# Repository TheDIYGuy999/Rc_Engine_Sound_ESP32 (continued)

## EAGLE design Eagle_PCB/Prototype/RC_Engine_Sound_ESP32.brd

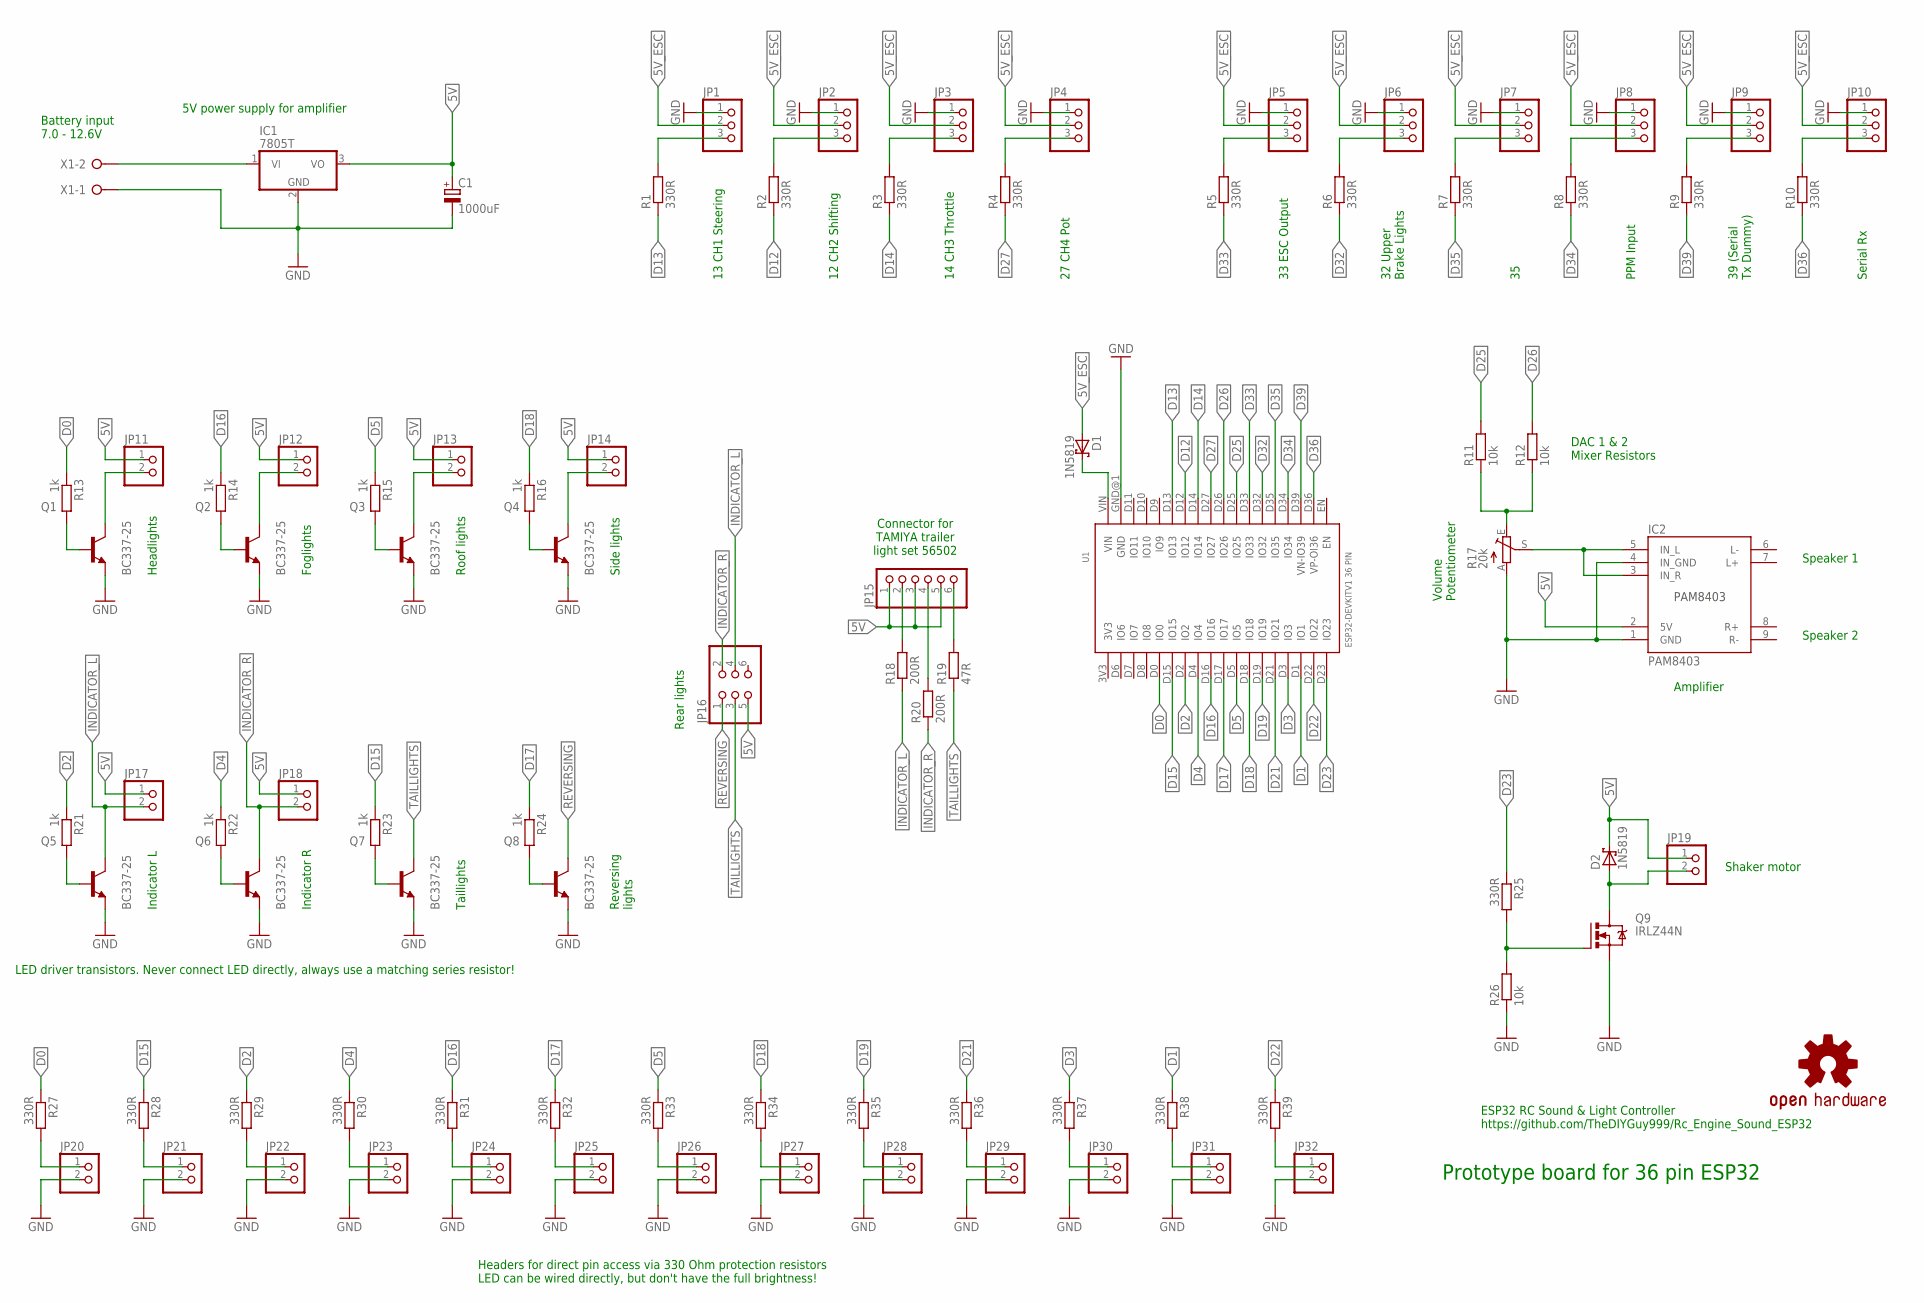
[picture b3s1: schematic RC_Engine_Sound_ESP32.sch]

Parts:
C1: 1000uF; E5-10,5
D1, D2: 1N5819; DO35-7
IC1: 7805T; TO220H
IC2: PAM8403
JP1, JP2, JP3, JP4, JP5, JP6, JP7, JP8, JP9, JP10: PINHD-1X3; 1X03
JP11, JP12, JP13, JP14, JP17, JP18, JP19, JP20, JP21, JP22, JP23, JP24, JP25, JP26, JP27, JP28, JP29, JP30, JP31, JP32: PINHD-1X2; 1X02
JP15: PINHD-1X6; 1X06
JP16: PINHD-2X3; 2X03
LOGO1: OSHW-LOGOM; OSHW-LOGO-M
Q1, Q2, Q3, Q4, Q5, Q6, Q7, Q8: BC337-25; TO92
Q9: IRLZ44N; TO220BV
R1, R2, R3, R4, R5, R6, R7, R8, R9, R10, R25, R27, R28, R29, R30, R31, R32, R33, R34, R35, R36, R37, R38, R39: 330R; 0207/2V
R11, R12: 10k; 0207/10
R13, R14, R15, R16, R21, R22, R23, R24: 1k; 0207/2V
R17: 20k; S64W
R18, R20: 200R; 0207/2V
R19: 47R; 0207/2V
R26: 10k; 0207/2V
U1: ESP32DEVKITV1; ESP32-DEVKITV1
X1: W237-02P; W237-132

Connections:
5V: C1.+, D2.C, IC1.3 (VO), IC2.2 (5V), JP11.1, JP12.1, JP13.1, JP14.1, JP15.1, JP15.3, JP15.5, JP16.5, JP17.1, JP18.1, JP19.1
5V_ESC: D1.A, JP1.2, JP2.2, JP3.2, JP4.2, JP5.2, JP6.2, JP7.2, JP8.2, JP9.2, JP10.2
BAT+: IC1.1 (VI), X1.2
D1: R38.1, U1.D1 (IO1)
D2: R21.1, R29.1, U1.D2 (IO2)
D4: R22.1, R30.1, U1.D4 (IO4)
D5: R15.1, R33.1, U1.D5 (IO5)
D12: R2.1, U1.D12 (IO12)
D13: R1.1, U1.D13 (IO13)
D14: R3.1, U1.D14 (IO14)
D15: R23.1, R28.1, U1.D15 (IO15)
D16: R14.1, R31.1, U1.D16 (IO16)
D17: R24.1, R32.1, U1.D17 (IO17)
D18: R16.1, R34.1, U1.D18 (IO18)
D19: R35.1, U1.D19 (IO19)
D21: R36.1, U1.D21 (IO21)
D22: R39.1, U1.D22 (IO22)
D23: R25.1, U1.D23 (IO23)
D25: R11.2, U1.D25 (IO25)
D26: R12.2, U1.D26 (IO26)
D27: R4.1, U1.D27 (IO27)
D32: R6.1, U1.D32 (IO32)
D33: R5.1, U1.D33 (IO33)
D34: R8.1, U1.D34 (IO34)
D35: R7.1, U1.D35 (IO35)
D36: R10.1, U1.D36 (VP-OI36)
D39: R9.1, U1.D39 (VN-IO39)
GND: C1.-, IC1.2 (GND), IC2.1 (GND), IC2.4 (IN_GND), JP1.1, JP2.1, JP3.1, JP4.1, JP5.1, JP6.1, JP7.1, JP8.1, JP9.1, JP10.1, JP20.2, JP21.2, JP22.2, JP23.2, JP24.2, JP25.2, JP26.2, JP27.2, JP28.2, JP29.2, JP30.2, JP31.2, JP32.2, Q1.1 (E), Q2.1 (E), Q3.1 (E), Q4.1 (E), Q5.1 (E), Q6.1 (E), Q7.1 (E), Q8.1 (E), Q9.S, R17.A, R26.1, U1.GND@1 (GND), X1.1
INDICATOR_L: JP16.4, JP17.2, Q5.3 (C), R18.1
INDICATOR_R: JP16.2, JP18.2, Q6.3 (C), R20.1
unnamed: IC2.3 (IN_R), IC2.5 (IN_L), R17.S
unnamed: R11.1, R12.1, R17.E
unnamed: JP1.3, R1.2
unnamed: Q9.G, R25.2, R26.2
unnamed: JP2.3, R2.2
unnamed: JP3.3, R3.2
unnamed: JP4.3, R4.2
unnamed: JP5.3, R5.2
unnamed: D1.C, U1.VIN
unnamed: JP6.3, R6.2
unnamed: JP7.3, R7.2
unnamed: JP8.3, R8.2
unnamed: JP9.3, R9.2
unnamed: JP10.3, R10.2
unnamed: D2.A, JP19.2, Q9.D
unnamed: Q1.2 (B), R13.2
unnamed: Q2.2 (B), R14.2
unnamed: JP11.2, Q1.3 (C)
unnamed: JP12.2, Q2.3 (C)
unnamed: Q7.2 (B), R23.2
unnamed: JP15.2, R18.2
unnamed: Q5.2 (B), R21.2
unnamed: JP15.4, R20.2
unnamed: Q6.2 (B), R22.2
unnamed: JP15.6, R19.2
unnamed: Q8.2 (B), R24.2
unnamed: Q3.2 (B), R15.2
unnamed: JP13.2, Q3.3 (C)
unnamed: Q4.2 (B), R16.2
unnamed: JP14.2, Q4.3 (C)
unnamed: JP21.1, R28.2
unnamed: JP22.1, R29.2
unnamed: JP23.1, R30.2
unnamed: JP24.1, R31.2
unnamed: JP25.1, R32.2
unnamed: JP26.1, R33.2
unnamed: JP27.1, R34.2
unnamed: JP28.1, R35.2
unnamed: JP29.1, R36.2
unnamed: JP30.1, R37.2
unnamed: JP31.1, R38.2
unnamed: JP32.1, R39.2
unnamed: JP20.1, R27.2
REVERSING: JP16.1, Q8.3 (C)
TAILLIGHTS: JP16.3, Q7.3 (C), R19.1

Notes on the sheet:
Speaker 1
Speaker 2
13 CH1 Steering
12 CH2 Shifting
14 CH3 Throttle
27 CH4 Pot
33 ESC Output
32 Upper Brake Lights
PPM Input
39 (Serial Tx Dummy)
Serial Rx
DAC 1 & 2 Mixer Resistors
Amplifier
Volume Potentiometer
5V power supply for amplifier
Battery input 7.0 - 12.6V
Prototype board for 36 pin ESP32
Shaker motor
Headlights
Foglights
Taillights
Indicator L
Indicator R
Roof lights
Side lights
Reversing lights
Connector for TAMIYA trailer light set 56502
Rear lights
ESP32 RC Sound & Light Controller https://github.com/TheDIYGuy999/Rc_Engine_Sound_ESP32
Headers for direct pin access via 330 Ohm protection resistors LED can be wired directly, but don't have the full brightness!
LED driver transistors. Never connect LED directly, always use a matching series resistor!

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
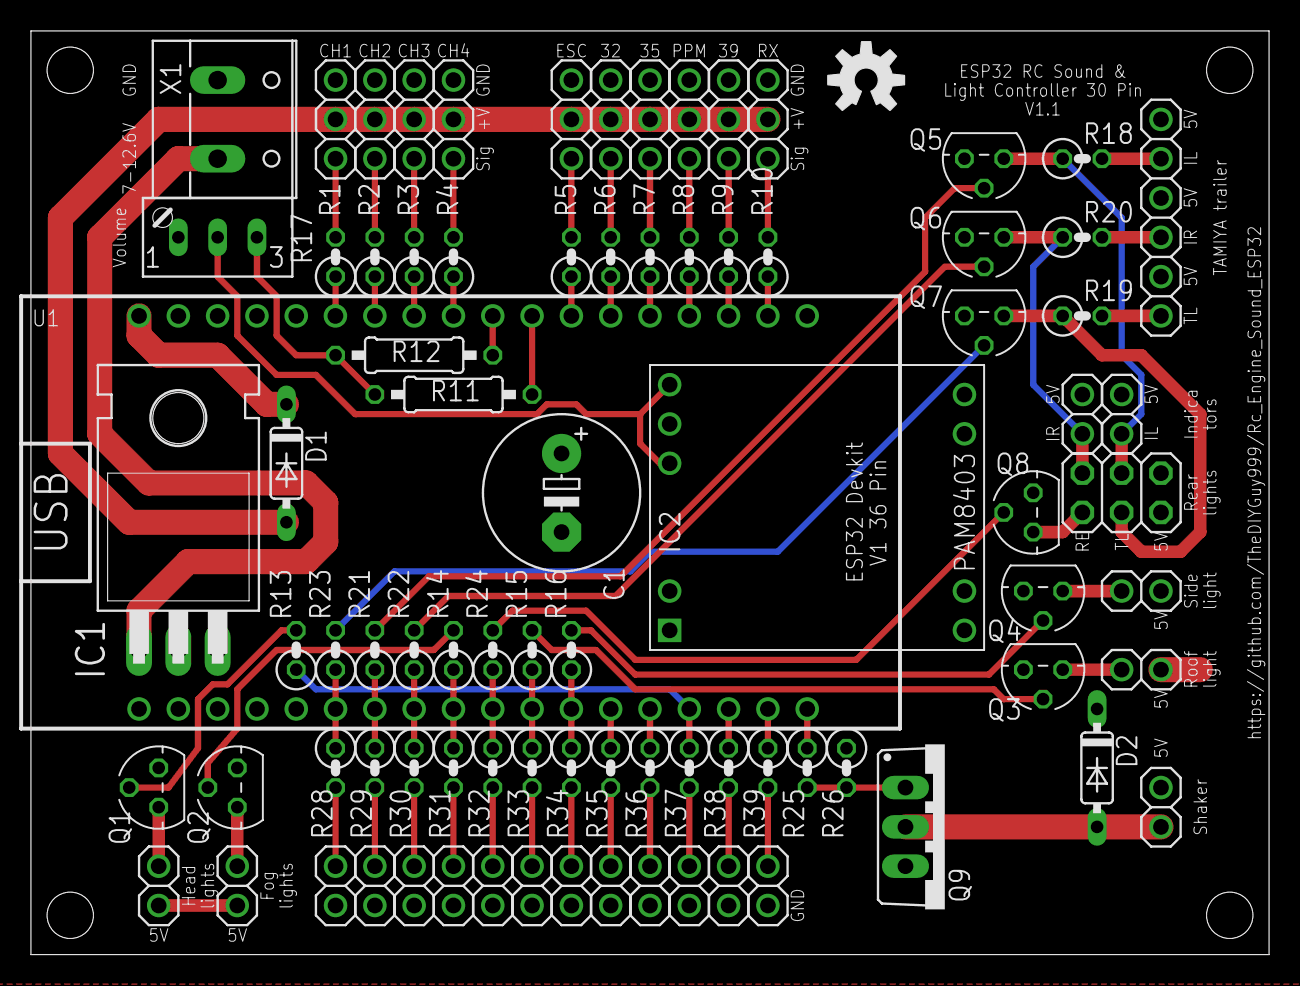
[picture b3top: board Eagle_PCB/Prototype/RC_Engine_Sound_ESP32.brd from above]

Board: 2 copper layers, 80.0 x 59.7 mm, 86 parts (0 on the bottom side), 75 nets.

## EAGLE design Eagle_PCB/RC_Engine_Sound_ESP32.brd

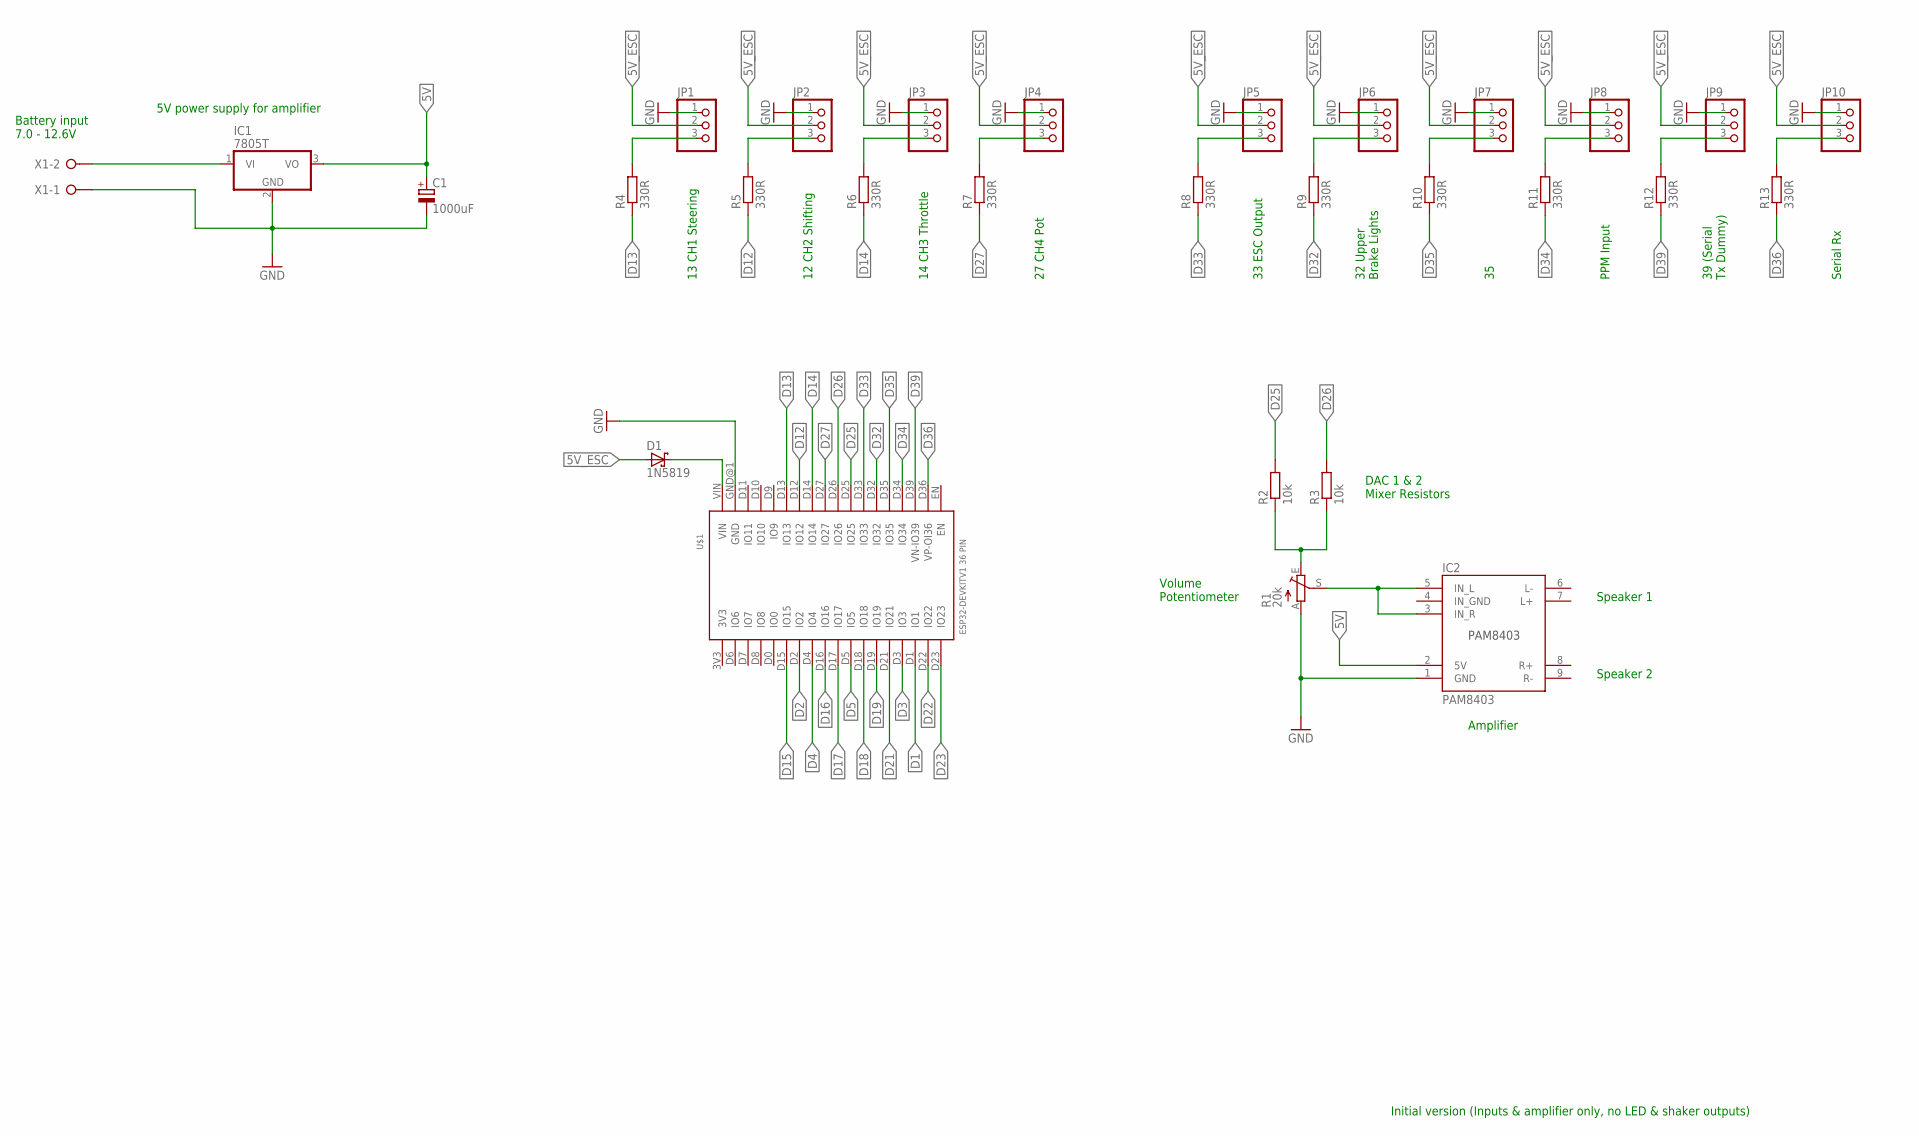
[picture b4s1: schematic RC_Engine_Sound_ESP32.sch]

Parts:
C1: 1000uF; E5-10,5
D1: 1N5819; DO35-7
IC1: 7805T; TO220H
IC2: PAM8403
JP1, JP2, JP3, JP4, JP5, JP6, JP7, JP8, JP9, JP10: PINHD-1X3; 1X03
R1: 20k; S64W
R2, R3: 10k; 0207/10
R4, R5, R6, R7, R8, R9, R10, R11, R12, R13: 330R; 0207/2V
U$1: ESP32DEVKITV1; ESP32-DEVKITV1
X1: W237-02P; W237-132

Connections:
5V: C1.+, IC1.3 (VO), IC2.2 (5V)
5V_ESC: D1.A, JP1.2, JP2.2, JP3.2, JP4.2, JP5.2, JP6.2, JP7.2, JP8.2, JP9.2, JP10.2
D1: U$1.D1 (IO1)
D2: U$1.D2 (IO2)
D3: U$1.D3 (IO3)
D4: U$1.D4 (IO4)
D5: U$1.D5 (IO5)
D12: R5.1, U$1.D12 (IO12)
D13: R4.1, U$1.D13 (IO13)
D14: R6.1, U$1.D14 (IO14)
D15: U$1.D15 (IO15)
D16: U$1.D16 (IO16)
D17: U$1.D17 (IO17)
D18: U$1.D18 (IO18)
D19: U$1.D19 (IO19)
D21: U$1.D21 (IO21)
D22: U$1.D22 (IO22)
D23: U$1.D23 (IO23)
D25: R2.2, U$1.D25 (IO25)
D26: R3.2, U$1.D26 (IO26)
D27: R7.1, U$1.D27 (IO27)
D32: R9.1, U$1.D32 (IO32)
D33: R8.1, U$1.D33 (IO33)
D34: R11.1, U$1.D34 (IO34)
D35: R10.1, U$1.D35 (IO35)
D36: R13.1, U$1.D36 (VP-OI36)
D39: R12.1, U$1.D39 (VN-IO39)
GND: C1.-, IC1.2 (GND), IC2.1 (GND), JP1.1, JP2.1, JP3.1, JP4.1, JP5.1, JP6.1, JP7.1, JP8.1, JP9.1, JP10.1, R1.A, U$1.GND@1 (GND), X1.1
unnamed: IC2.3 (IN_R), IC2.5 (IN_L), R1.S
unnamed: R1.E, R2.1, R3.1
unnamed: JP1.3, R4.2
unnamed: IC1.1 (VI), X1.2
unnamed: JP2.3, R5.2
unnamed: JP3.3, R6.2
unnamed: JP4.3, R7.2
unnamed: JP5.3, R8.2
unnamed: D1.C, U$1.VIN
unnamed: JP6.3, R9.2
unnamed: JP7.3, R10.2
unnamed: JP8.3, R11.2
unnamed: JP9.3, R12.2
unnamed: JP10.3, R13.2

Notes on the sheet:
Speaker 1
Speaker 2
13 CH1 Steering
12 CH2 Shifting
14 CH3 Throttle
27 CH4 Pot
33 ESC Output
32 Upper Brake Lights
PPM Input
39 (Serial Tx Dummy)
Serial Rx
DAC 1 & 2 Mixer Resistors
Amplifier
Volume Potentiometer
5V power supply for amplifier
Battery input 7.0 - 12.6V
Initial version (Inputs & amplifier only, no LED & shaker outputs)

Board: 2 copper layers, 29 parts (0 on the bottom side), 29 nets, no tracks yet.

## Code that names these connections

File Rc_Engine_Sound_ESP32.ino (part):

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// ERROR CODES (INDICATOR LIGHTS)
// =======================================================================================================
//
/* Constantly on = no SBUS signal (check "sbusInverted" true / false in "2_adjustmentsRemote.h")
   Number of blinks = this channel signal is not between 1400 and 1600 microseconds and can't be auto calibrated
   (check channel trim settings)
*/
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// provides short circuit protection. Also works on the serial Rx pin "VP" (36)
// ------------------------------------------------------------------------------------

// Serial command pins for SBUS & IBUS -----
#define COMMAND_RX 36 // pin 36, labelled with "VP", connect it to "Micro RC Receiver" pin "TXO"
#define COMMAND_TX 39 // pin 39, labelled with "VN", only used as a dummy, not connected

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#define INDICATOR_LEFT_PIN 2 // Orange left indicator (turn signal) light
#define INDICATOR_RIGHT_PIN 4 // Orange right indicator (turn signal) light
#define FOGLIGHT_PIN 16 // (16 = RX2) Fog lights
#define REVERSING_LIGHT_PIN 17 // (TX2) White reversing light
#define ROOFLIGHT_PIN 5 // Roof lights (high beam, if "define SEPARATE_FULL_BEAM")
#define SIDELIGHT_PIN 18 // Side lights (connect roof ligthts here, if "define SEPARATE_FULL_BEAM")
#define BEACON_LIGHT2_PIN 19 // Blue beacons light
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#define COUPLER_SWITCH_PIN 32 // switch for trailer coupler sound
#endif

#define SHAKER_MOTOR_PIN 23 // Shaker motor (shaking truck while idling and engine start / stop)

#define DAC1 25 // connect pin25 (do not change the pin) to a 10kOhm resistor
#define DAC2 26 // connect pin26 (do not change the pin) to a 10kOhm resistor
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  static uint32_t curHornSample = 0;                           // Index of currently loaded horn sample
  static uint32_t curSirenSample = 0;                          // Index of currently loaded siren sample
  static uint32_t curSound1Sample = 0;                         // Index of currently loaded sound1 sample
  static uint32_t curReversingSample = 0;                      // Index of currently loaded reversing beep sample
  static uint32_t curIndicatorSample = 0;                      // Index of currently loaded indicator tick sample
  static uint32_t curWastegateSample = 0;                      // Index of currently loaded wastegate sample
  static uint32_t curBrakeSample = 0;                          // Index of currently loaded brake sound sample
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
#if not defined SPI_DASHBOARD
  sideLight.begin(SIDELIGHT_PIN, 8, 20000); // Timer 8, 20kHz
  beaconLight1.begin(BEACON_LIGHT1_PIN, 9, 20000); // Timer 9, 20kHz
  beaconLight2.begin(BEACON_LIGHT2_PIN, 10, 20000); // Timer 10, 20kHz
#endif

#if defined THIRD_BRAKLELIGHT
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  sbusInit = false;
  Serial.println("Initializing SBUS, check transmitter & receiver (sbusInverted true / false OK?)...");
  while (!sbusInit) {
    readSbusCommands(); // SBUS communication (pin 36)
  }
  Serial.println("SBUS initialization done!");

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    brakeLight.pwm(255 - crankingDim); // Brakelight on
  }
  else {
    tailLight.pwm(constrain(brightness - (crankingDim / 2), (brightness / 2), 255)); // Taillights (reduced brightness)
    brakeLight.pwm(constrain(brightness - (crankingDim / 2), (brightness / 2), 255)); // Brakelight (reduced brightness)
  }
}
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
    case 4: // roof & side & head & fog lights ---------------------------------------------------------------------
#ifdef NO_FOGLIGHTS
      lightsState = 5; // Skip foglights
#endif
      cabLight.off();
      sideLight.pwm(constrain(sideLightsBrightness - crankingDim, (sideLightsBrightness / 2), 255));
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void loop() {

#if defined SBUS_COMMUNICATION
  readSbusCommands(); // SBUS communication (pin 36)
  mcpwmOutput(); // PWM servo signal output

#elif defined IBUS_COMMUNICATION
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
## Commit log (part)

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2019-12-03 Initial version 0.1
2019-12-03 V0.2: many new sounds added
2019-12-05 V0.3: horn added, plays together with engine sound!
2019-12-07 V0.4: volume offset bug fixed, new sounds
2019-12-08 V0.4: volume offset bug fixed, new sounds, schematic
2019-12-09 V0.5: added PWM horn triggering option, Jaguar car and UP locomotive
2019-12-10 v0.6: fixed slow engine RPM response
2019-12-10 v0.7: "gap" bug between sounds in PWM mode fixed, 2 sounds in PWM mode
2019-12-10 v0.8: many new sounds, volume offset bug fixed again
2019-12-14 v0.9: Humvee Diesel sound and truck pneumatic brake release sound added
2019-12-15 v1.0: engine shut off sequence, truck air brakes
2019-12-16 v1.1: Truck reversing peep sound added
2019-12-17 v1.2: control for lights added
2019-12-22 v1.4: Indicator (turn signal) support added
2019-12-24 v1.51: solved redefinition issue
2019-12-27 v1.6: serial control mode added, more sounds, more lights
2019-12-31 v1.7: engine vibration shaker support added
2020-01-04 v1.8: throttle dependent engine volume, indicator ticking sound, new sounds
2020-01-10 v1.9: initial PPM input support for throttle and steering
2020-01-12 v2.0: Mack truck added, experimental features added, statusLED library update required!
2020-01-18 v2.1: adjustable turbo sound, Cat 3406B, VW beetle, indicator direction adjustable
2020-01-19 v2.2: vehicle mass simulation (ESC control) added, LED pins changed, Scania R620 sound
2020-01-19 v2.2: vehicle mass simulation (ESC control) added, LED pins changed, Scania R620 sound added
2020-01-20 v2.3: many detail optimisations like brake lights, reversing lights, air brake sound
2020-01-22 Minor reversing bug fixed, failsafe mode for Serial & PWM communication mode
2020-02-08 v2.5: 3rd brake light added, realistic top speed, smoother acceleration & deceleration
2020-02-20 v2.7: inertia simulation transmission gear dependent, new horns
2020-02-21 v2.8: virtual clutch added, variable acceleration speed, better brakes
2020-02-22 v2.9: throttle now automatically altered while TAMIYA 3 speed gearbox shifting
2020-02-23 v2.91: minor bugfixes according to readme.md
2020-02-24 v3.0: clutch engaging changed to prevent it from excessive slipping
2020-02-25 V3.1: Scania R620 & other sounds added
2020-02-27 V3.2: added wastegate, Unimog U 1000, AM General M35
2020-03-04 v3.3: many changes according to readme
2020-03-08 v3.4: separate Diesel knock with fixed sampling rate, many other changes
2020-03-14 v3.5: diesel knock triggering bug fixed, new sounds and more
2020-03-15 Cooling fan sound, Tatra 813 V12, Scania 50 ton added
2020-03-15 v3.6: Cooling fan sound, Tatra 813 V12, Scania 50 ton added
2020-03-20 v3.61: Tatra 813 optimised, new fan & knock sounds
2020-03-28 v3.7 now supporting 30 pin ESP32 board as well
2020-03-30 Schematic now including PCB layout (for 36 pin ESP32)
2020-03-30 v3.8 automatic transmission simulation, PCB files!
2020-03-31 Gerber files included, mounting holes now recognised properly in Gerber export
2020-03-31 PCB pictures added
2020-04-05 Final PCB for 30 pin ESP32 available!
2020-04-10 Removed faulty Gerber file
2020-04-10 Solved board issues after assembling of first PCB
2020-04-11 v3.9: SBUS protocol added, optimised Detroit Diesel
2020-04-11 schematic replaced
2020-04-13 v4.0: failsafe for SBUS implemented
2020-04-16 PCB v1.1: moved R28 away from trailer connector
2020-05-02 v4.1: automatic 4 speed transmission with torque converter
2020-05-02 v4.11: automatic 4 speed transmission with torque converter
2020-05-03 v4.12: Further automatic transmission fine tuning
2020-05-09 v4.2: 3, 4 or 6 gears & adaptive shift points for automatic transmission & more
2020-05-16 v4.3: double clutch transmission added, automatic shifting strategy refined
2020-05-24 v4.4: adaptive knock volume, Jeep track hawk , DAF XF added
2020-06-12 Add files via upload
    These sounds were created from the video of an IS-3 here: https://youtu.be/0EyhRHdySJs
2020-07-14 v4.5: CATERPILLAR_MODE (dual throttle input) for tanks, diggers etc.
2020-07-14 v4.6: tank cannon sound & flash added
2020-07-18 BOM (Components List) added
2020-07-21 BOM (Components List) updated
2020-07-26 v4.7: experimental support for rcTrigger library added
2020-07-30 v4.8: throttle fader, documentation, supercharger, improved Jeep trackhawk
2020-08-04 v.4.82: Missing Ural files aded
2020-08-04 v4.82: Missing files for Ural 2 setting added
2020-08-07 v4.9: knock usable in combination with rev. sound, Messerschmitt Bf 109 added
2020-08-23 v5.0: sichtung between idle and rev sound now working seamlessly
2020-08-23 v5.0: switching between idle and rev sound now working seamlessly
2020-08-23 v5.01: CAT 3408 Peterbilt added, configuration error solved
2020-08-24 v5.01: better documentation (software upload etc.)
2020-08-28 v5.1: Jake brake, gearbox neutral, adjustable volume, high / low beam for headlights, new W900A sounds
2020-08-29 v5.1: more functions, more sounds
2020-09-06 v5.2 preview: IBUS experimental support, easier vehicle selection, better sound
2020-09-16 v5.2 preview 2 added (beta)
2020-09-18 v5.2 preview 3 added (beta 2)
2020-09-18 v5.2 preview 4 added (beta 3)
2020-09-20 v5.4 major update
    Many improvements according to README.md
2020-09-20 v5.2: optimised README.md
    Note, that "v5.4" is wrong
2020-09-20 v5.2: Optimised README.md
2020-09-22 blowoff comment added
2020-09-22 README.md optimised
2020-09-23 v5.3: PWM now faster, Kirovets K700
    PWM performance issues solved, 5 channels instead of 4, improved and new vehicles
2020-09-23 renamed
2020-09-25 v5.4: Volvo FH16, Cummins 12V, R6 knock pattern
2020-10-07 v5.5: channel assignment, virtual 3 speed manual
2020-10-09 v5.6: variable duration horn & siren
2020-11-01 v5.7: new SMD PCB, 16 gears, soft switching indicators
2020-11-06 v5.8: MAN TGX 680, SMD board v1.1
2020-11-21 v6.0: optimised CAT3408, pigs
2020-11-25 Gerbers.zip BOM error fixed
2020-11-30 v6.1: changes according to README.md
2020-12-07 now including "How To Order Your PCB.pdf"
2020-12-08 v6.2: changes according to README.md
2020-12-12 Quick start manual added
2021-01-16 v6.3: changes according to changelog
2021-01-20 v6.4: outputs for steering & shifting servo
2021-02-14 v6.5: macOS Big Sur fix
2021-02-24 v6.6: new fifth wheel options
2021-03-02 v6.61: 'couplingSampleCount' bug fixed
2021-03-06 v6.62: ESC state machine lockup bug fixed
2021-03-07 v6.63: trailer sound fixes
2021-03-13 v6.7: MAN KAT military truck added
2021-03-14 v6.8: STEERING_RAMP_TIME for scale steering movements
2021-03-15 v6.81: bugfixes according to changelog
2021-05-08 v6.9: new horn melodies, GMC sierra, Volvo FH, new engine brake option
2021-05-30 v7.0: many changes according to changelog
2021-05-31 v7.1: shifting servo output usable with automatic transmission
2021-06-03 v7.2: Unimog engine brake, bugfixes, indicators as debugger
2021-06-05 v7.3: many updates according to changelog
2021-06-19 v7.4: new remote profiles and more. See changelog
2021-06-27 v7.5: many improvements according to README.md
2021-08-14 v7.6: many changes according to README.md
2021-08-22 v7.7: LCD dashboard, Neopixels, SUMD support
2021-08-29 v7.8: Excavator support added
2021-09-22 v8.0: Many changes and bugfixes according to README.md
2021-09-25 v8.1: variable tire squeal
2021-10-08 v8.11: serious PWM mode bug fixed, other minor changes
2021-10-24 v8.2: Visual Studio Code support. Directory structure changed!
    for details see change log in README.md
2021-10-25 comments added
2021-11-07 v8.3: wireless trailer lights
2021-11-14 v8.4: Magirus Deutz 256 sound, new parameters, sounds reworked
2021-11-17 v8.5: multiple wireless trailer support and much more. See change log
2021-11-18 v8.6: Magirus Mercur 125 air cooled V6 Diesel truck sound
2021-12-05 v8.7: new vehicles and options according to change log
2021-12-18 new SMD board added, trailer SW update v0.3
2021-12-19 New board picture added
2021-12-24 TFT_eSPI library version specified
2022-01-01 v8.8: faster steering servo movement, new 5th wheel option
2022-02-16 v8.9: new wireless trailer lights option
2022-02-27 v9.0: AIRPLANE_MODE, trailer ramps ESC mode
2022-03-29 Improved serial output and debug info, fixed a few typos
2022-04-10 Add dependency on 5th wheel
    #define TRAILER_LIGHTS_TRAILER_PRESENCE_WHILE_5TH_WHEEL_LOCKED to be added in 10_adjustmentsTrailer.h
2022-04-18 Added comment for Flysky i6 configuration
2022-04-19 Servo Debug Typo fixed
2022-04-22 v9.1: Benford Dumper, semi automatic transmission and more
2022-04-22 Added ESPNOW_DEBUG option printing additional debug messages.
2022-05-08 Added Arduino header to every vehicle config file.
2022-05-08 Fixed some sound file (.h) names (mostly upper/lower case typos).
2022-05-08 v9.2: board definition 1.0.6 now compatible, Neopixel animations
2022-05-12 v 9.3: support for RZ7886 motor driver IC, more ESC parameters
2022-05-18 v 9.4: SBUS baudrate adjustable, ticking noise fixed
2022-05-27 v9.5: battery low discharge protection and more, see change log
2022-05-30 v9.6.0: Out of fuel message, KITT sound, optimized semi automatic
2022-06-06 v9.7.0: many changes according to change log
2022-06-17 v9.8.0: switchable crawler mode
2022-06-25 v9.9.0 manch changes according to README.md
2022-06-30 v9.9.1: SBUS & battery protection bugfixes
2022-07-01 Extracted Changelog From README
2022-07-11 v9.10.0: STEAM_LOCOMOTIVE_MODE see change log
2022-12-31 v9.11.0: LS3 Defender etc.
2023-01-09 Readme changed
2023-02-04 v9.12.0 beta: configuration website
2023-02-04 link to trailer software added
2023-02-04 documentation changed
2023-02-05 v9.12.0 beta 2
2023-02-08 lowered WiFi power, less noise in speaker
2023-02-12 v9.12.0 beta 3: adjustable WiFi power and more
2023-05-04 v9.12.0
2023-05-14 9.13.0-b1 ESC adjustable on 192.168.4.1, Neopixels on CH 4
2023-05-18 v9.13.0-b1: more ESC adjustments, Frevic dashboard
2023-05-18 v9.13.0-b3: no engine lagging anymore with Frevic dash
2023-05-19 v9.13.0-b4: servo positions adjustable on website
2023-05-20 v9.13.0-b5: first light settings on configuration website
2023-05-29 v9.13.0-b6: more configurable light options
2023-06-01 v9.13.0-b7: more light options, Neopixel modes dropdown
2023-08-16 Fix filenames with special characters
    Change the filenames so that Arduino IDE 2 does not complaint about
    them.
2023-08-26 Fix sound volume calculation
    Three issues are fixed:
    1.
    in a lot of cases the last sample is not handled.
    if (sampleCount < sampleLength-1)
    will omit the last sample.
    2.
2023-08-26 Fix processor load issue
    Testing showed that the timer interrupts use each 25us and
    have a period (at idle) of 50us.
    That means a processor load at more than 100% at idle with pwm inputs.
    Turns out the DAC write is using a spin lock for port access which
    we don't need.
    See https://forum.arduino.cc/t/esp32-dacwrite-ersetzen/653954/5
2023-08-26 Remove resetting the sample rate for the fixed timer
    Resetting the timer frequency takes around 3us.
    This is unnecessary for the fixed timer.
    We just need to tell the users to keep the same sample
    rate for every additional sound (which we kind of already do.)
    Else you would have issues anyways, when playing e.g. a horn
    and indicator light ticks at the same time.
2023-08-26 Update all vehicles with the new sound volumes.
    I actually used a script for this.
    Indicate if you want to have that to automatically
    convert.
2023-09-06 Fix sample end logic
2023-09-13 Fix knock volume
2024-01-21 Ferguson TEA20 tractor added
2024-01-21 playing with L120H loader
2024-01-21 Playing with Volvo L120H
2024-01-22 L120H hydraulic flow sound
2024-01-28 L120H adjusted
2024-03-23 v9.13
2024-03-26 Update README.md
    File Description added
2024-03-26 Update README.md
    bts7960 HW extension added
2024-03-28 Update 2_Remote.h
    Added PS3 Bluetooth functionality
2024-08-24 V9.13.0. many changes according to changelog
2024-08-24 v9.14.0_b1: first CAT 730 implementation
2024-08-25 V9.14.0-b2: CAT 730 now with dump hydraulic sound
2026-03-14 v9.14.0: many changes according to Changelog.md
    - Documentation files in German added
    - Documentation Files made by Frikkie Bester added
    - Mercedes SK 1935 V8 truck added
    - Mercedes SK 1838 V8 truck added
    - Rough terrain crane added
    - CRANE_MODE added (many hydraulic channels)
2026-03-15 9.15.0-b1: CAT D6 implemented
